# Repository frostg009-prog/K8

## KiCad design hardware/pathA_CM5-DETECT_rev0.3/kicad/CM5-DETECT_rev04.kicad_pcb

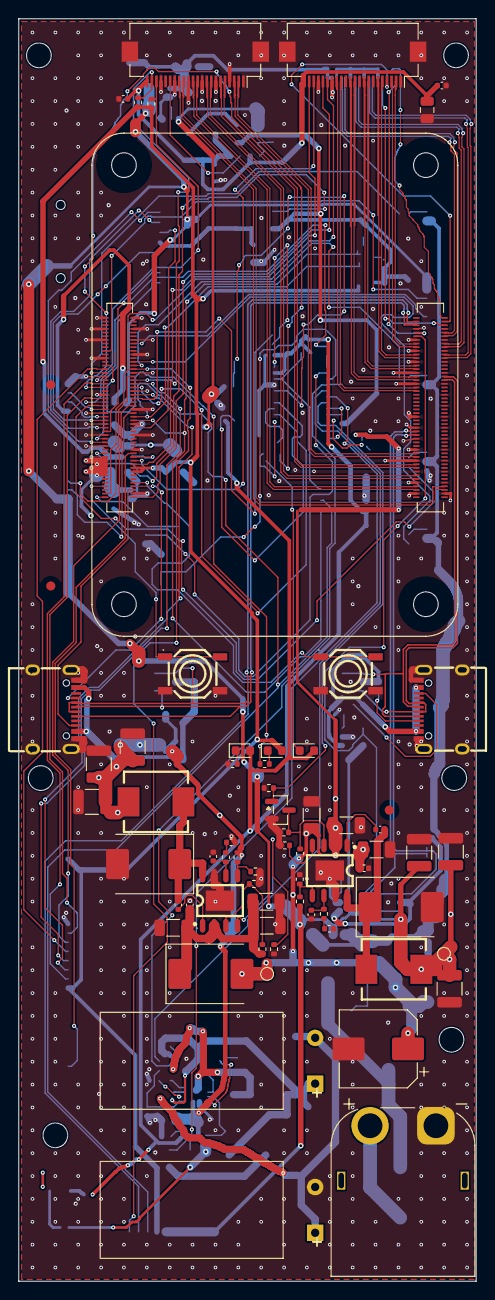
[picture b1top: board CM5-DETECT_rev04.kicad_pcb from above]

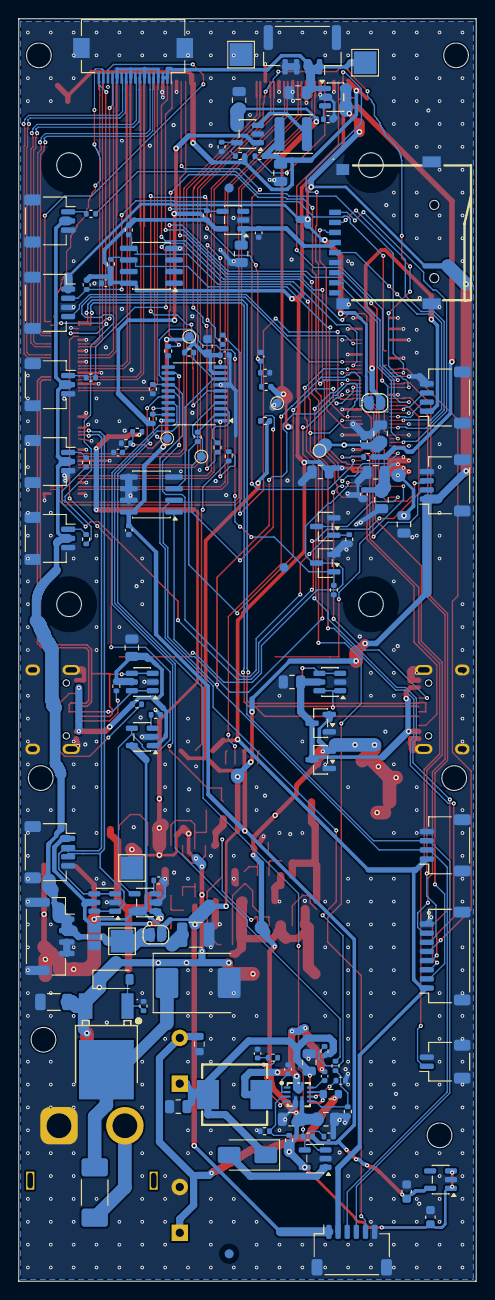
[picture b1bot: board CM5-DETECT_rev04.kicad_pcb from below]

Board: 4 copper layers, 50.0 x 138.0 mm, 204 parts (131 on the bottom side), 157 nets.

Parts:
C1, C2, C3, C4, C30, C31, C32, C33, C40, C42, C44: 22uF; C_0805_2012Metric
C5, C6, C9, C13, C16, C23, C26, C35, C46, C47, C49, C50, C52, C53, C54: 100nF; C_0402_1005Metric
C7, C39, C41, C43, C45, C48: 10uF; C_0805_2012Metric
C8, C10, C11, C12, C20, C21, C22: 2.2uF 100V; C_1206_3216Metric
C14, C24: 8.2nF; C_0402_1005Metric
C15, C25: 100pF; C_0402_1005Metric
C17, C18, C19, C27, C28, C29, C55: 47uF 16V; C_1210_3225Metric
C34: 2.2uF; C_0402_1005Metric
C36: 4.7nF; C_0402_1005Metric
C37, C38, C51: 1uF; C_0603_1608Metric
C_BULK: 100uF 50V low-ESR; CP_Elec_8x10
D_B1, D_B2: SS510C 5A 100V Schottky; D_SMC
D_B1IN: SS510C (blocks hold-up back-feed); D_SMC
D_CHG: SS34 (cap max 4.8 V = 2.4 V/cell); D_SMA
D_ERR: LED red ERROR; LED_0603_1608Metric
D_PWR: LED green PWR; LED_0603_1608Metric
D_RPZ: BZT52C12 Vgs clamp; D_SOD-123
D_RUN: LED blue RUN; LED_0603_1608Metric
D_TVS: SMCJ33A TVS 1.5kW; D_SMC
F1: 10A fast 2410 125V; Fuse_2410
FID1, FID2, FID3, FID4, FID5, FID6: fiducial; Fiducial_1mm_Mask2mm
H1, H2, H3, H4, H5, H6: M2.5; MountingHole_2.7mm_M2.5_ISO14580
JP_MATEK: close = 5V to Matek pin1; SolderJumper-2_P1.3mm_Open_RoundedPad1.0x1.5mm
JP_SERVO: close = servos from 5V_AUX (<=1.5 A tota; SolderJumper-2_P1.3mm_Open_RoundedPad1.0x1.5mm
J_AIPWR: AI POWER 5V (5V,5V,GND,GND) JST-GH for H; JST_GH_SM04B-GHS-TB_1x04-1MP_P1.25mm_Horizontal
J_BAT: XT60PW-M (battery 3S-6S); AMASS_XT60PW-M_1x02_P7.20mm_Horizontal
J_CAM1: CAM1 MIPI CSI-2 4-lane FFC 22p 0.5mm (Pi; Hirose_FH12-22S-0.5SH_1x22-1MP_P0.50mm_Horizontal
J_CAM2: CAM2 MIPI CSI-2 4-lane FFC 22p 0.5mm (Pi; Hirose_FH12-22S-0.5SH_1x22-1MP_P0.50mm_Horizontal
J_FAN: FAN 5V PWM (5V,PWM,GND,TACH); JST_SH_SM04B-SRSS-TB_1x04-1MP_P1.00mm_Horizontal
J_GPS: GPS/TELEM UART2 (5V,TX,RX,GND); JST_SH_SM04B-SRSS-TB_1x04-1MP_P1.00mm_Horizontal
J_I2C: I2C1 (3V3,SCL,SDA,GND); JST_SH_SM04B-SRSS-TB_1x04-1MP_P1.00mm_Horizontal
J_IO: GPIO (3V3,G7,G10,G11,G16,G17,G24,GND); JST_SH_SM08B-SRSS-TB_1x08-1MP_P1.00mm_Horizontal
J_MATEK: MATEK UART0 (5V*,TX,RX,GND); JST_SH_SM04B-SRSS-TB_1x04-1MP_P1.00mm_Horizontal
J_PCIE: PCIe x1 FFC 16p (Pi 5 pinout) -> Hailo A; Hirose_FH12-16S-0.5SH_1x16-1MP_P0.50mm_Horizontal
J_RTC: RTC battery 3V (+,-); JST_SH_SM02B-SRSS-TB_1x02-1MP_P1.00mm_Horizontal
J_S1: SERVO1 (SIG,V+,GND); JST_SH_SM03B-SRSS-TB_1x03-1MP_P1.00mm_Horizontal
J_S2: SERVO2 (SIG,V+,GND); JST_SH_SM03B-SRSS-TB_1x03-1MP_P1.00mm_Horizontal
J_S3: SERVO3 (SIG,V+,GND); JST_SH_SM03B-SRSS-TB_1x03-1MP_P1.00mm_Horizontal
J_S4: SERVO4 (SIG,V+,GND); JST_SH_SM03B-SRSS-TB_1x03-1MP_P1.00mm_Horizontal
J_SD: microSD push-push TF-01A; TF-SMD_TF-01A
J_SPWR: SERVO POWER IN from BEC (V+,V+,GND,GND); JST_GH_SM04B-GHS-TB_1x04-1MP_P1.25mm_Horizontal
J_THA: THERMAL AUX (5V,3V3,SCL,SDA,SYNC,GND); JST_SH_SM06B-SRSS-TB_1x06-1MP_P1.00mm_Horizontal
J_THU: THERMAL USB (VBUS,D-,D+,GND); JST_SH_SM04B-SRSS-TB_1x04-1MP_P1.00mm_Horizontal
J_USB1: USB-C #1 FW/PC (rpiboot + USB gadget); USB-C-SMD_TYPE-C-16PIN-2MD-073
J_USB2: USB-C #2 HOST; USB-C-SMD_TYPE-C-16PIN-2MD-073
L_B1, L_B2: 6.8uH 6A FXL0630-6R8-M; IND-SMD_L7.0-W6.6
L_C33: 2.2uH 2.3A FNR4012S2R2MT; L_Changjiang_FNR4012S
L_HB: 2.2uH 9.5A SLO0650H2R2MTT; IND-SMD_L7.1-W6.6_SLO0650H
M1: Raspberry Pi CM5 (CM5108032 / CM5116032; Raspberry-Pi-5-Compute-Module
Q_AUX_OFF: 2N7002; SOT-23
Q_PMIC: 2N7002 -> CM5 PMIC_EN (hard reset); SOT-23
Q_PWB: 2N7002 -> CM5 PWR_BUT (wake / clean off); SOT-23
Q_RP: NCE60P12K P-MOS 60V reverse-polarity; TO-252-2_L6.5-W6.1-P4.58-LS10.0-TL
R1: 47k; R_0402_1005Metric
R2, R4, R10, R16, R18, R25, R49, R50: 100k; R_0402_1005Metric
R3, R9, R15, R27, R36, R42, R43, R44, R45, R46, R47, R48, R56: 10k; R_0402_1005Metric
R5, R11: 18k; R_0402_1005Metric
R6, R12: 249k; R_0402_1005Metric
R7, R13: 10.5k; R_0402_1005Metric
R8, R14: 53.6k; R_0402_1005Metric
R17, R30, R31: 6.8k; R_0402_1005Metric
R19, R20: 10k; R_0603_1608Metric
R21: 340k; R_0402_1005Metric
R22: 107k; R_0402_1005Metric
R23: 30k; R_0402_1005Metric
R24: 127k; R_0402_1005Metric
R26: 45.3k; R_0402_1005Metric
R28, R29: 56k; R_0402_1005Metric
R32: 3.4k; R_0402_1005Metric
R33, R34, R35, R51, R52: 2.2k; R_0402_1005Metric
R37, R38, R39, R40, R41, R53, R55: 1k; R_0402_1005Metric
R54, R57, R58, R59, R60: 220R; R_0402_1005Metric
R_VREF: 0R; R_0402_1005Metric
SC1: 10F 2.7V supercap (Jianghai SCCDQR2R7106; SuperCap_D10_L20_Horizontal
SC2: 10F 2.7V supercap; SuperCap_D10_L20_Horizontal
SW_BOOT: BOOT (nRPIBOOT); SW-SMD_4P-L5.2-W5.2-P3.70-LS6.4
SW_PWR: POWER (PWR_BUT); SW-SMD_4P-L5.2-W5.2-P3.70-LS6.4
TP_3V3: 3V3; TestPoint_Pad_D1.0mm
TP_5V: 5V; TestPoint_Pad_D1.0mm
TP_5VA: 5VA; TestPoint_Pad_D1.0mm
TP_AI5V: wire pad AI +5V; TestPoint_Pad_2.5x2.5mm
TP_AIGND: wire pad AI GND; TestPoint_Pad_2.5x2.5mm
TP_GND: GND; TestPoint_Pad_D1.0mm
TP_RST: RST; TestPoint_Pad_D1.0mm
TP_SRVG: wire pad servo GND; TestPoint_Pad_2.5x2.5mm
TP_SRVV: wire pad servo V+ (BEC); TestPoint_Pad_2.5x2.5mm
TP_SWIO: SWIO; TestPoint_Pad_D1.0mm
TP_VIN: VIN; TestPoint_Pad_D1.0mm
U_AON: ME6211C33M5G LDO 3.3V; SOT-23-5
U_B1, U_B2: RT6365GSP 60V 5A buck (alt SCT2650STER); SOP-8_L5.0-W3.9-P1.27-LS6.0-BL-EP
U_C33: SY8089A1AAC 2A buck 3.3V cameras; SOT-23-5
U_CHG: SY6280AAC supercap charger 1A; SOT-23-5
U_ESD1, U_ESD2, U_ESD3: USBLC6-2SC6 ESD; SOT-23-6
U_HB: SGM6611C boost 7A (hold-up 5.03 V); VQFN-11_L2.5-W2.0-P0.50-TL_TI_RNR
U_ID1, U_ID2: CH213K ideal diode VBUS1->5V; SOT-23
U_MCU: CH32V003F4P6 supervisor (HW watchdog, po; TSSOP-20_4.4x6.5mm_P0.65mm
U_SD: RT9742GGJ5 SD power switch; TSOT-23-5
U_SEC: ATECC608B secure element (I2C 0x60); SOIC-8_3.9x4.9mm_P1.27mm
U_TEMP: NST175H temp sensor 0x48; SOIC-8_3.9x4.9mm_P1.27mm
U_VB2, U_VB3: SY6280AAC VBUS switch 1A; SOT-23-5
U_VB4: SY6280AAC 5V for AI board 2A; SOT-23-5

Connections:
+3V3_AON: C38.1, C50.1, C51.1, C53.1, D_ERR.2, D_PWR.2, R18.2, R43.2, R44.2, TP_3V3.1, U_AON.5, U_MCU.9, U_TEMP.8
+3V3_CAM: C40.1, C45.1, C46.1, C47.1, J_CAM1.22, J_CAM2.22, L_C33.2, R26.1, R33.2
+3V3_CM5: C7.1, C54.1, D_RUN.2, J_I2C.1, J_IO.1, J_THA.2, M1.84, M1.86, R34.2, R35.2, R36.2, R42.2, R51.2, R52.2, R56.2, R_VREF.2, U_C33.1, U_SD.5, U_SEC.8
+5V_AI: C44.1, J_AIPWR.1, J_AIPWR.2, J_PCIE.1, J_PCIE.2, TP_AI5V.1, U_VB4.1
+5V_AUX: C27.1, C28.1, C29.1, JP_MATEK.2, JP_SERVO.2, J_FAN.1, J_GPS.1, J_THA.1, L_B2.2, R14.1, TP_5VA.1, U_VB2.5, U_VB3.5, U_VB4.4, U_VB4.5
+5V_CM5: C1.1, C2.1, C3.1, C4.1, C5.1, C6.1, C17.1, C18.1, C19.1, C32.1, C33.1, C37.1, C39.1, L_B1.2, M1.77, M1.79, M1.81, M1.83, M1.85, M1.87, R8.1, R21.1, R45.1, TP_5V.1, U_AON.1, U_AON.3, U_C33.4, U_CHG.5, U_HB.6, U_ID1.2, U_ID2.2
AUX_OFF: Q_AUX_OFF.1, R16.1, U_MCU.17
B1_BOOT: C16.1, U_B1.1
B1_CC: C14.1, R7.2
B1_COMP: C15.1, R7.1, U_B1.6
B1_EN: R4.2, R5.1, U_B1.3
B1_FB: R8.2, R9.1, U_B1.5
B1_RT: R6.1, U_B1.4
B1_SW: C16.2, D_B1.1, L_B1.1, U_B1.8
B2_BOOT: C26.1, U_B2.1
B2_CC: C24.1, R13.2
B2_COMP: C25.1, R13.1, U_B2.6
B2_EN: Q_AUX_OFF.3, R10.2, R11.1, U_B2.3
B2_FB: R14.2, R15.1, U_B2.5
B2_RT: R12.1, U_B2.4
B2_SW: C26.2, D_B2.1, L_B2.1, U_B2.8
C33_FB: R26.2, R27.1, U_C33.5
C33_LX: L_C33.1, U_C33.3
CAM1_C_N: J_CAM1.8, M1.127
CAM1_C_P: J_CAM1.9, M1.129
CAM1_D0_N: J_CAM1.2, M1.115
CAM1_D0_P: J_CAM1.3, M1.117
CAM1_D1_N: J_CAM1.5, M1.121
CAM1_D1_P: J_CAM1.6, M1.123
CAM1_D2_N: J_CAM1.11, M1.133
CAM1_D2_P: J_CAM1.12, M1.135
CAM1_D3_N: J_CAM1.14, M1.139
CAM1_D3_P: J_CAM1.15, M1.141
CAM1_GPIO0: J_CAM1.17, M1.97
CAM1_GPIO1: J_CAM1.18, M1.100
CAM1_SCL: J_CAM1.20, M1.80
CAM1_SDA: J_CAM1.21, M1.82
CAM2_C_N: J_CAM2.8, M1.187
CAM2_C_P: J_CAM2.9, M1.189
CAM2_D0_N: J_CAM2.2, M1.175
CAM2_D0_P: J_CAM2.3, M1.177
CAM2_D1_N: J_CAM2.5, M1.181
CAM2_D1_P: J_CAM2.6, M1.183
CAM2_D2_N: J_CAM2.11, M1.193
CAM2_D2_P: J_CAM2.12, M1.195
CAM2_D3_N: J_CAM2.14, M1.194
CAM2_D3_P: J_CAM2.15, M1.196
CAM2_EN: J_CAM2.17, R33.1
CAM2_SCL: J_CAM2.20, M1.35, R34.1
CAM2_SDA: J_CAM2.21, M1.36, R35.1
CHG_ISET: R17.1, U_CHG.3
CM5_ON_SENSE: R42.1, U_MCU.19
FAN_PWM: J_FAN.2, M1.19, R56.1
FAN_TACH: J_FAN.4, M1.16
GND: C1.2, C2.2, C3.2, C4.2, C5.2, C6.2, C7.2, C8.2, C9.2, C10.2, C11.2, C12.2, C13.2, C14.2, C15.2, C17.2, C18.2, C19.2, C20.2, C21.2, C22.2, C23.2, C24.2, C25.2, C27.2, C28.2, C29.2, C30.2, C31.2, C32.2, C33.2, C34.2, C36.2, C37.2, C38.2, C39.2, C40.2, C41.2, C42.2, C43.2, C44.2, C45.2, C46.2, C47.2, C48.2, C49.2, C50.2, C51.2, C52.2, C53.2, C54.2, C55.2, C_BULK.2, D_B1.2, D_B2.2, D_TVS.2, J_AIPWR.3, J_AIPWR.4, J_AIPWR.MP, J_BAT.1, J_CAM1.1, J_CAM1.4, J_CAM1.7, J_CAM1.10, J_CAM1.13, J_CAM1.16, J_CAM1.19, J_CAM1.MP, J_CAM2.1, J_CAM2.4, J_CAM2.7, J_CAM2.10, J_CAM2.13, J_CAM2.16, J_CAM2.19, J_CAM2.MP, J_FAN.3, J_FAN.MP, J_GPS.4, J_GPS.MP, J_I2C.4, J_I2C.MP, J_IO.8, J_IO.MP, J_MATEK.4, J_MATEK.MP, J_PCIE.3, J_PCIE.6, J_PCIE.9, J_PCIE.12, J_PCIE.MP, J_RTC.2, J_RTC.MP, J_S1.3, J_S1.MP, J_S2.3, J_S2.MP, J_S3.3, J_S3.MP, J_S4.3, J_S4.MP, J_SD.6, J_SD.10, J_SD.11, J_SD.12, J_SD.13, J_SPWR.3, J_SPWR.4, J_SPWR.MP, J_THA.6, J_THA.MP, J_THU.4, J_THU.MP, J_USB1.13, J_USB1.14, J_USB1.A1B12, J_USB1.B1A12, J_USB2.13, J_USB2.14, J_USB2.A1B12, J_USB2.B1A12, M1.1, M1.2, M1.7, M1.8, M1.13, M1.14, M1.22, M1.23, M1.32, M1.33, M1.42, M1.43, M1.52, M1.53, M1.59, M1.60, M1.65, M1.66, M1.71, M1.74, M1.98, M1.107, M1.108, M1.113, M1.114, M1.119, M1.120, M1.125, M1.126, M1.131, M1.132, M1.137, M1.138, M1.144, M1.150, M1.155, M1.156, M1.161, M1.162, M1.167, M1.168, M1.173, M1.174, M1.179, M1.180, M1.185, M1.186, M1.191, M1.192, M1.197, M1.198, Q_AUX_OFF.2, Q_PMIC.2, Q_PWB.2, R1.2, R3.2, R5.2, R6.2, R9.2, R11.2, R12.2, R15.2, R16.2, R17.2, R20.2, R22.2, R24.2, R25.2, R27.2, R30.2, R31.2, R32.2, R46.2, R48.2, R49.2, R50.2, R53.2, SC2.2, SW_BOOT.3, SW_BOOT.4, SW_PWR.3, SW_PWR.4, TP_AIGND.1, TP_GND.1, TP_SRVG.1, U_AON.2, U_B1.7, U_B1.9, U_B2.7, U_B2.9, U_C33.2, U_CHG.2, U_ESD1.2, U_ESD2.2, U_ESD3.2, U_HB.5, U_ID1.1, U_ID2.1, U_MCU.7, U_SD.2, U_SEC.4, U_TEMP.4, U_TEMP.5, U_TEMP.6, U_TEMP.7, U_VB2.2, U_VB3.2, U_VB4.2
GPIO_VREF: M1.78, R_VREF.1
HB_BOOT: C35.1, U_HB.10
HB_CC: C36.1, R23.2
HB_COMP: R23.1, U_HB.4
HB_FB: R21.2, R22.1, U_HB.3
HB_ILIM: R24.1, U_HB.8
HB_SW: C35.2, L_HB.2, U_HB.11
HB_VCC: C34.1, U_HB.2
HEARTBEAT: M1.46, R39.2
HEARTBEAT_R: R39.1, U_MCU.10
HOLD_EN: R25.1, R41.2, U_HB.7
HOLD_EN_R: R41.1, U_MCU.15
I2C1_SCL: J_I2C.2, J_THA.3, M1.56, R52.1, U_SEC.6, U_TEMP.2
I2C1_SDA: J_I2C.3, J_THA.4, M1.58, R51.1, U_SEC.5, U_TEMP.1
IO_GPIO7: J_IO.2, M1.37
IO_GPIO10: J_IO.3, M1.44
IO_GPIO11: J_IO.4, M1.38
IO_GPIO16: J_IO.5, M1.29
IO_GPIO17: J_IO.6, M1.50
IO_GPIO24: J_IO.7, M1.45
LEDE_K: D_ERR.1, R55.1
LEDP_K: D_PWR.1, R53.1
LEDR_K: D_RUN.1, R54.1
LED_ERR_N: R55.2, U_MCU.1
LED_RUN_N: M1.27, R54.2
MATEK_5V: JP_MATEK.1, J_MATEK.1
MCU_NRST: R43.1, TP_RST.1, U_MCU.4
MCU_RX: M1.39, R38.2
MCU_RX_R: R38.1, U_MCU.3
MCU_SWIO: TP_SWIO.1, U_MCU.18
MCU_TX: M1.40, R37.2
MCU_TX_R: R37.1, U_MCU.2
NRPIBOOT: M1.93, SW_BOOT.1, SW_BOOT.2
PCIE_CLKREQ_N: J_PCIE.15, M1.102
PCIE_CLK_N: J_PCIE.5, M1.112
PCIE_CLK_P: J_PCIE.4, M1.110
PCIE_DET_WAKE: J_PCIE.14, M1.104
PCIE_PWR_EN: J_PCIE.13, M1.106
PCIE_RST_N: J_PCIE.16, M1.109
PCIE_RX_N: J_PCIE.8, M1.118
PCIE_RX_P: J_PCIE.7, M1.116
PCIE_TX_N: J_PCIE.11, M1.124
PCIE_TX_P: J_PCIE.10, M1.122
PFAIL_N: M1.47, R40.2
PFAIL_R: R40.1, U_MCU.11
PMIC_EN: M1.99, Q_PMIC.3
PMIC_OFF: Q_PMIC.1, R49.1, U_MCU.12
PWRBTN_PRESS: Q_PWB.1, R50.1, U_MCU.13
PWR_BUT: M1.92, Q_PWB.3, SW_PWR.1, SW_PWR.2
QRP_G: D_RPZ.2, Q_RP.1, R1.1
SCAP_CHG: D_CHG.2, U_CHG.1
SCAP_CHG_EN: R18.1, U_CHG.4, U_MCU.16
SCAP_MID: R19.2, R20.1, SC1.2, SC2.1
SD_CLK: J_SD.5, M1.57
SD_CMD: J_SD.3, M1.62
SD_D0: J_SD.7, M1.63
SD_D1: J_SD.8, M1.67
SD_D2: J_SD.1, M1.69
SD_D3: J_SD.2, M1.61
SD_PWR_ON: M1.75, R36.1, U_SD.4
SD_VDD: C48.1, C49.1, J_SD.4, U_SD.1
SERVO1: J_S1.1, R57.2
SERVO1_G: M1.31, R57.1
SERVO2: J_S2.1, R58.2
SERVO2_G: M1.28, R58.1
SERVO3: J_S3.1, R59.2
SERVO3_G: M1.49, R59.1
SERVO4: J_S4.1, R60.2
SERVO4_G: M1.26, R60.1
TEMP_ALERT: R44.1, U_MCU.8, U_TEMP.3
THU_DN: J_THU.2, M1.165, U_ESD3.3, U_ESD3.4
THU_DP: J_THU.3, M1.163, U_ESD3.1, U_ESD3.6
TH_SYNC: J_THA.5, M1.30
UART0_RX: J_MATEK.3, M1.51
UART0_TX: J_MATEK.2, M1.55
UART2_RX: J_GPS.3, M1.34
UART2_TX: J_GPS.2, M1.54
USB1_CC1: J_USB1.A5, M1.94
USB1_CC2: J_USB1.B5, M1.96
USB1_DN: J_USB1.A7, J_USB1.B7, M1.103, U_ESD1.3, U_ESD1.4
USB1_DP: J_USB1.A6, J_USB1.B6, M1.105, U_ESD1.1, U_ESD1.6
USB2_CC1: J_USB2.A5, R28.1
USB2_CC2: J_USB2.B5, R29.1
USB2_DN: J_USB2.A7, J_USB2.B7, M1.136, U_ESD2.3, U_ESD2.4
USB2_DP: J_USB2.A6, J_USB2.B6, M1.134, U_ESD2.1, U_ESD2.6
V5_SENSE: C52.1, R45.2, R46.1, U_MCU.6
VB2_ISET: R30.1, U_VB2.3
VB3_ISET: R31.1, U_VB3.3
VB4_ISET: R32.1, U_VB4.3
VBAT_F: D_TVS.1, F1.2, Q_RP.4
VBAT_RAW: F1.1, J_BAT.2
VBAT_RTC: J_RTC.1, M1.76
VBAT_SENSE: C9.1, R2.2, R3.1, U_MCU.20
VBUS1: C41.1, J_USB1.A4B9, J_USB1.B4A9, U_ESD1.5, U_ID1.3, U_ID2.3
VBUS2: C42.1, J_USB2.A4B9, J_USB2.B4A9, R28.2, R29.2, U_ESD2.5, U_VB2.1
VBUS3: C43.1, J_THU.1, U_ESD3.5, U_VB3.1
VBUS_EN: M1.111, U_VB2.4, U_VB3.4
VIN_B1: C10.1, C11.1, C12.1, C13.1, D_B1IN.1, R4.1, U_B1.2
VIN_PROT: C8.1, C20.1, C21.1, C22.1, C23.1, C_BULK.1, D_B1IN.2, D_RPZ.1, Q_RP.3, R2.1, R10.1, TP_VIN.1, U_B2.2
VSCAP: C30.1, C31.1, D_CHG.1, L_HB.1, R19.1, R47.1, SC1.1, U_HB.9
VSCAP_SENSE: R47.2, R48.1, U_MCU.14
VSERVO: C55.1, JP_SERVO.1, J_S1.2, J_S2.2, J_S3.2, J_S4.2, J_SPWR.1, J_SPWR.2, TP_SRVV.1

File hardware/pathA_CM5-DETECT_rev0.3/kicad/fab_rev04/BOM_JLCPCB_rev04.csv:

Comment,Designator,Footprint,LCSC Part #
22uF,"C1,C2,C3,C4,C30,C31,C32,C33,C40,C42,C44",C_0805_2012Metric,C45783
100nF,"C5,C6,C9,C13,C16,C23,C26,C35,C46,C47,C49,C50,C52,C53,C54",C_0402_1005Metric,C1525
10uF,"C7,C39,C41,C43,C45,C48",C_0805_2012Metric,C15850
2.2uF 100V,"C8,C10,C11,C12,C20,C21,C22",C_1206_3216Metric,C170101
8.2nF,"C14,C24",C_0402_1005Metric,C45186
100pF,"C15,C25",C_0402_1005Metric,C1546
47uF 16V,"C17,C18,C19,C27,C28,C29,C55",C_1210_3225Metric,C77101
2.2uF,C34,C_0402_1005Metric,C12530
4.7nF,C36,C_0402_1005Metric,C1538
1uF,"C37,C38,C51",C_0603_1608Metric,C15849
100uF 50V low-ESR,C_BULK,CP_Elec_8x10,C48935390
SS510C (blocks hold-up back-feed),D_B1IN,D_SMC,C19229
SS510C 5A 100V Schottky,"D_B1,D_B2",D_SMC,C19229
SS34 (cap max 4.8 V = 2.4 V/cell),D_CHG,D_SMA,C8678
LED red ERROR,D_ERR,LED_0603_1608Metric,C2286
LED green PWR,D_PWR,LED_0603_1608Metric,C12624
BZT52C12 Vgs clamp,D_RPZ,D_SOD-123,C43491
LED blue RUN,D_RUN,LED_0603_1608Metric,C2288
SMCJ33A TVS 1.5kW,D_TVS,D_SMC,C152083
10A fast 2410 125V,F1,Fuse_2410,C2838934
"AI POWER 5V (5V,5V,GND,GND) for Hailo HAT",J_AIPWR,JST_SH_SM04B-SRSS-TB_1x04-1MP_P1.00mm_Horizontal,C160404
XT60PW-M (battery 3S-6S),J_BAT,AMASS_XT60PW-M_1x02_P7.20mm_Horizontal,C98732
CAM1 MIPI CSI-2 4-lane FFC 22p 0.5mm (Pi 5 / CM5IO pinout),J_CAM1,Hirose_FH12-22S-0.5SH_1x22-1MP_P0.50mm_Horizontal,C597981
CAM2 MIPI CSI-2 4-lane FFC 22p 0.5mm (Pi 5 / CM5IO pinout),J_CAM2,Hirose_FH12-22S-0.5SH_1x22-1MP_P0.50mm_Horizontal,C597981
"FAN 5V PWM (5V,PWM,GND,TACH)",J_FAN,JST_SH_SM04B-SRSS-TB_1x04-1MP_P1.00mm_Horizontal,C160404
"GPS/TELEM UART2 (5V,TX,RX,GND)",J_GPS,JST_SH_SM04B-SRSS-TB_1x04-1MP_P1.00mm_Horizontal,C160404
"I2C1 (3V3,SCL,SDA,GND)",J_I2C,JST_SH_SM04B-SRSS-TB_1x04-1MP_P1.00mm_Horizontal,C160404
"GPIO (3V3,G7,G10,G11,G16,G17,G24,GND)",J_IO,JST_SH_SM08B-SRSS-TB_1x08-1MP_P1.00mm_Horizontal,C160408
"MATEK UART0 (5V*,TX,RX,GND)",J_MATEK,JST_SH_SM04B-SRSS-TB_1x04-1MP_P1.00mm_Horizontal,C160404
PCIe x1 FFC 16p (Pi 5 pinout) -> Hailo AI HAT+/M.2 HAT+,J_PCIE,Hirose_FH12-16S-0.5SH_1x16-1MP_P0.50mm_Horizontal,C596731
"RTC battery 3V (+,-)",J_RTC,JST_SH_SM02B-SRSS-TB_1x02-1MP_P1.00mm_Horizontal,C160402
"SERVO1 (SIG,V+,GND)",J_S1,JST_SH_SM03B-SRSS-TB_1x03-1MP_P1.00mm_Horizontal,C160403
"SERVO2 (SIG,V+,GND)",J_S2,JST_SH_SM03B-SRSS-TB_1x03-1MP_P1.00mm_Horizontal,C160403
"SERVO3 (SIG,V+,GND)",J_S3,JST_SH_SM03B-SRSS-TB_1x03-1MP_P1.00mm_Horizontal,C160403
"SERVO4 (SIG,V+,GND)",J_S4,JST_SH_SM03B-SRSS-TB_1x03-1MP_P1.00mm_Horizontal,C160403
microSD push-push TF-01A,J_SD,TF-SMD_TF-01A,C91145
"SERVO POWER IN from BEC (V+,V+,GND,GND)",J_SPWR,JST_SH_SM04B-SRSS-TB_1x04-1MP_P1.00mm_Horizontal,C160404
"THERMAL AUX (5V,3V3,SCL,SDA,SYNC,GND)",J_THA,JST_SH_SM06B-SRSS-TB_1x06-1MP_P1.00mm_Horizontal,C160406
"THERMAL USB (VBUS,D-,D+,GND)",J_THU,JST_SH_SM04B-SRSS-TB_1x04-1MP_P1.00mm_Horizontal,C160404
USB-C #1 FW/PC (rpiboot + USB gadget),J_USB1,USB-C-SMD_TYPE-C-16PIN-2MD-073,C2765186
USB-C #2 HOST,J_USB2,USB-C-SMD_TYPE-C-16PIN-2MD-073,C2765186
6.8uH 6A FXL0630-6R8-M,"L_B1,L_B2",IND-SMD_L7.0-W6.6,C167221
2.2uH 2.3A FNR4012S2R2MT,L_C33,L_Changjiang_FNR4012S,C167776
2.2uH 9.5A SLO0650H2R2MTT,L_HB,IND-SMD_L7.1-W6.6_SLO0650H,C216163
Raspberry Pi CM5 (CM5108032 / CM5116032 / Lite),M1,Raspberry-Pi-5-Compute-Module,
2N7002,Q_AUX_OFF,SOT-23,C8545
2N7002 -> CM5 PMIC_EN (hard reset),Q_PMIC,SOT-23,C8545
2N7002 -> CM5 PWR_BUT (wake / clean off),Q_PWB,SOT-23,C8545
NCE60P12K P-MOS 60V reverse-polarity,Q_RP,TO-252-2_L6.5-W6.1-P4.58-LS10.0-TL,C326372
47k,R1,R_0402_1005Metric,C25792
100k,"R2,R4,R10,R16,R18,R25,R49,R50",R_0402_1005Metric,C25741
10k,"R3,R9,R15,R27,R36,R42,R43,R44,R45,R46,R47,R48,R56",R_0402_1005Metric,C25744
18k,"R5,R11",R_0402_1005Metric,C25762
249k,"R6,R12",R_0402_1005Metric,C2998084
10.5k,"R7,R13",R_0402_1005Metric,C25850
53.6k,"R8,R14",R_0402_1005Metric,C5153961
6.8k,"R17,R30,R31",R_0402_1005Metric,C93940
10k,"R19,R20",R_0603_1608Metric,C25804
340k,R21,R_0402_1005Metric,C2933090
107k,R22,R_0402_1005Metric,C25743
30k,R23,R_0402_1005Metric,C25776
127k,R24,R_0402_1005Metric,C25751
45.3k,R26,R_0402_1005Metric,C2933099
56k,"R28,R29",R_0402_1005Metric,C25796
3.4k,R32,R_0402_1005Metric,C4940
2.2k,"R33,R34,R35",R_0402_1005Metric,C25879
1k,"R37,R38,R39,R40,R41,R53,R55",R_0402_1005Metric,C11702
220R,"R54,R57,R58,R59,R60",R_0402_1005Metric,C25091
0R,R_VREF,R_0402_1005Metric,C17168
10F 2.7V supercap (Jianghai SCCDQR2R7106 / Kamcap),SC1,SuperCap_D10_L20_Horizontal,
10F 2.7V supercap,SC2,SuperCap_D10_L20_Horizontal,
BOOT (nRPIBOOT),SW_BOOT,SW-SMD_4P-L5.2-W5.2-P3.70-LS6.4,C42420254
POWER (PWR_BUT),SW_PWR,SW-SMD_4P-L5.2-W5.2-P3.70-LS6.4,C42420254
ME6211C33M5G LDO 3.3V,U_AON,SOT-23-5,C82942
RT6365GSP 60V 5A buck (alt SCT2650STER),"U_B1,U_B2",SOP-8_L5.0-W3.9-P1.27-LS6.0-BL-EP,C3024482
SY8089A1AAC 2A buck 3.3V cameras,U_C33,SOT-23-5,C479074
SY6280AAC supercap charger 1A,U_CHG,SOT-23-5,C55136
USBLC6-2SC6 ESD,"U_ESD1,U_ESD2,U_ESD3",SOT-23-6,C2827654
SGM6611C boost 7A (hold-up 5.03 V),U_HB,VQFN-11_L2.5-W2.0-P0.50-TL_TI_RNR,C699669
CH213K ideal diode VBUS1->5V,"U_ID1,U_ID2",SOT-23,C5456874
"CH32V003F4P6 supervisor (HW watchdog, power-fail)",U_MCU,TSSOP-20_4.4x6.5mm_P0.65mm,C5187096
RT9742GGJ5 SD power switch,U_SD,TSOT-23-5,C250547
ATECC608B secure element (I2C 0x60),U_SEC,SOIC-8_3.9x4.9mm_P1.27mm,C1518769
NST175H temp sensor 0x48,U_TEMP,SOIC-8_3.9x4.9mm_P1.27mm,C917444
SY6280AAC VBUS switch 1A,"U_VB2,U_VB3",SOT-23-5,C55136
SY6280AAC 5V for AI board 2A,U_VB4,SOT-23-5,C55136

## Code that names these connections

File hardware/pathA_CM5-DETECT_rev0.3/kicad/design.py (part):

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cm5 = {str(p): 'GND' for p in GND_CM5}
for p in (77, 79, 81, 83, 85, 87):
    cm5[str(p)] = '+5V_CM5'
cm5.update({'84': '+3V3_CM5', '86': '+3V3_CM5', '78': 'GPIO_VREF', '76': 'VBAT_RTC',
            '94': 'USB1_CC1', '96': 'USB1_CC2', '103': 'USB1_DN', '105': 'USB1_DP',
            '134': 'USB2_DP', '136': 'USB2_DN', '163': 'THU_DP', '165': 'THU_DN', '111': 'VBUS_EN',
            '102': 'PCIE_CLKREQ_N', '104': 'PCIE_DET_WAKE', '106': 'PCIE_PWR_EN', '109': 'PCIE_RST_N',
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            '115': 'CAM1_D0_N', '117': 'CAM1_D0_P', '121': 'CAM1_D1_N', '123': 'CAM1_D1_P',
            '127': 'CAM1_C_N', '129': 'CAM1_C_P', '133': 'CAM1_D2_N', '135': 'CAM1_D2_P',
            '139': 'CAM1_D3_N', '141': 'CAM1_D3_P', '80': 'CAM1_SCL', '82': 'CAM1_SDA',
            '97': 'CAM1_GPIO0', '100': 'CAM1_GPIO1',
            # CAM2 = MIPI1 (DPHY1), I2C on ID_SC/ID_SD (GPIO1/GPIO0) like CM5IO with J6 fitted
            '175': 'CAM2_D0_N', '177': 'CAM2_D0_P', '181': 'CAM2_D1_N', '183': 'CAM2_D1_P',
            '187': 'CAM2_C_N', '189': 'CAM2_C_P', '193': 'CAM2_D2_N', '195': 'CAM2_D2_P',
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            '19': 'FAN_PWM', '16': 'FAN_TACH', '92': 'PWR_BUT', '93': 'NRPIBOOT', '99': 'PMIC_EN',
            '57': 'SD_CLK', '62': 'SD_CMD', '63': 'SD_D0', '67': 'SD_D1', '69': 'SD_D2', '61': 'SD_D3',
            '75': 'SD_PWR_ON'})
GPIO_NET = {2: 'I2C1_SDA', 3: 'I2C1_SCL', 4: 'UART2_TX', 5: 'UART2_RX', 6: 'TH_SYNC', 7: 'IO_GPIO7',
            8: 'MCU_RX', 9: 'MCU_TX', 10: 'IO_GPIO10', 11: 'IO_GPIO11', 12: 'SERVO1_G', 13: 'SERVO2_G',
            14: 'UART0_TX', 15: 'UART0_RX', 16: 'IO_GPIO16', 17: 'IO_GPIO17', 18: 'SERVO3_G',
            19: 'SERVO4_G', 20: 'LED_RUN_N', 22: 'HEARTBEAT', 23: 'PFAIL_N', 24: 'IO_GPIO24'}
for g, n in GPIO_NET.items():
    cm5[str(GPIO_PIN[g])] = n

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add('M1', 'CM5IO:Raspberry-Pi-5-Compute-Module', 'Raspberry Pi CM5 (CM5108032 / CM5116032 / Lite)',
    'Amphenol 10164227-1001A1RLF x2 (C6782225)', cm5,
    'Two 100-pin board-to-board connectors are soldered at the factory; CM5 is plugged in and screwed (4xM2.5)')
R('0R', 'GPIO_VREF', '+3V3_CM5', note='GPIO bank voltage = 3.3 V', ref='R_VREF')
for i in range(4):
    Cap('22uF', '+5V_CM5', fp=C0805, lcsc='C45783', note='CM5 5V input bulk', near='M1.81')
Cap('100nF', '+5V_CM5', near='M1.79'); Cap('100nF', '+5V_CM5', near='M1.85')
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        'alt HCTL XW05202-220R-00 (C2906120); cable 22p 0.5 mm up to 300-400 mm')


cam(1, 'CAM1_SCL', 'CAM1_SDA', 'CAM1_GPIO0', 'CAM1_GPIO1')
cam(2, 'CAM2_SCL', 'CAM2_SDA', 'CAM2_EN', '')
R('2.2k', 'CAM2_EN', '+3V3_CAM', note='camera 2 power enable (as CM5IO)')
R('2.2k', 'CAM2_SCL', '+3V3_CM5'); R('2.2k', 'CAM2_SDA', '+3V3_CM5')
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    {1: 'LED_ERR_N', 2: 'MCU_TX_R', 3: 'MCU_RX_R', 4: 'MCU_NRST', 5: '', 6: 'V5_SENSE', 7: 'GND',
     8: 'TEMP_ALERT', 9: '+3V3_AON', 10: 'HEARTBEAT_R', 11: 'PFAIL_R', 12: 'PMIC_OFF', 13: 'PWRBTN_PRESS',
     14: 'VSCAP_SENSE', 15: 'HOLD_EN_R', 16: 'SCAP_CHG_EN', 17: 'AUX_OFF', 18: 'MCU_SWIO', 19: 'CM5_ON_SENSE',
     20: 'VBAT_SENSE'})   # rev0.4: VBAT_SENSE on PD3/A4 (was PA1), PA1 = NC, WDT_DIS jumper removed (UART command W0)
Cap('100nF', '+3V3_AON', near='U_MCU.9'); Cap('1uF', '+3V3_AON', fp=C0603, near='U_MCU.9')
R('1k', 'MCU_TX_R', 'MCU_TX', note='series: no back-feed when CM5 is off')
R('1k', 'MCU_RX_R', 'MCU_RX'); R('1k', 'HEARTBEAT_R', 'HEARTBEAT'); R('1k', 'PFAIL_R', 'PFAIL_N')
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add('J_GPS', GH(4), 'GPS/TELEM UART2 (5V,TX,RX,GND)', GH_LCSC[4], {1: '+5V_AUX', 2: 'UART2_TX', 3: 'UART2_RX', 4: 'GND', 'MP': 'GND'})
add('J_I2C', GH(4), 'I2C1 (3V3,SCL,SDA,GND)', GH_LCSC[4], {1: '+3V3_CM5', 2: 'I2C1_SCL', 3: 'I2C1_SDA', 4: 'GND', 'MP': 'GND'})
add('J_IO', GH(8), 'GPIO (3V3,G7,G10,G11,G16,G17,G24,GND)', GH_LCSC[8],
    {1: '+3V3_CM5', 2: 'IO_GPIO7', 3: 'IO_GPIO10', 4: 'IO_GPIO11', 5: 'IO_GPIO16', 6: 'IO_GPIO17', 7: 'IO_GPIO24', 8: 'GND', 'MP': 'GND'})
add('J_FAN', GH(4), 'FAN 5V PWM (5V,PWM,GND,TACH)', GH_LCSC[4], {1: '+5V_AUX', 2: 'FAN_PWM', 3: 'GND', 4: 'FAN_TACH', 'MP': 'GND'})
R('10k', 'FAN_PWM', '+3V3_CM5')
add('J_RTC', GH(2), 'RTC battery 3V (+,-)', GH_LCSC[2], {1: 'VBAT_RTC', 2: 'GND', 'MP': 'GND'})
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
